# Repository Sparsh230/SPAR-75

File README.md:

# SPAR-75
A 75% keyboard 

Schmetic:

Keyboard matricks:

PCB:

3D model:

Cad Model Assembly(Plateless Mount):

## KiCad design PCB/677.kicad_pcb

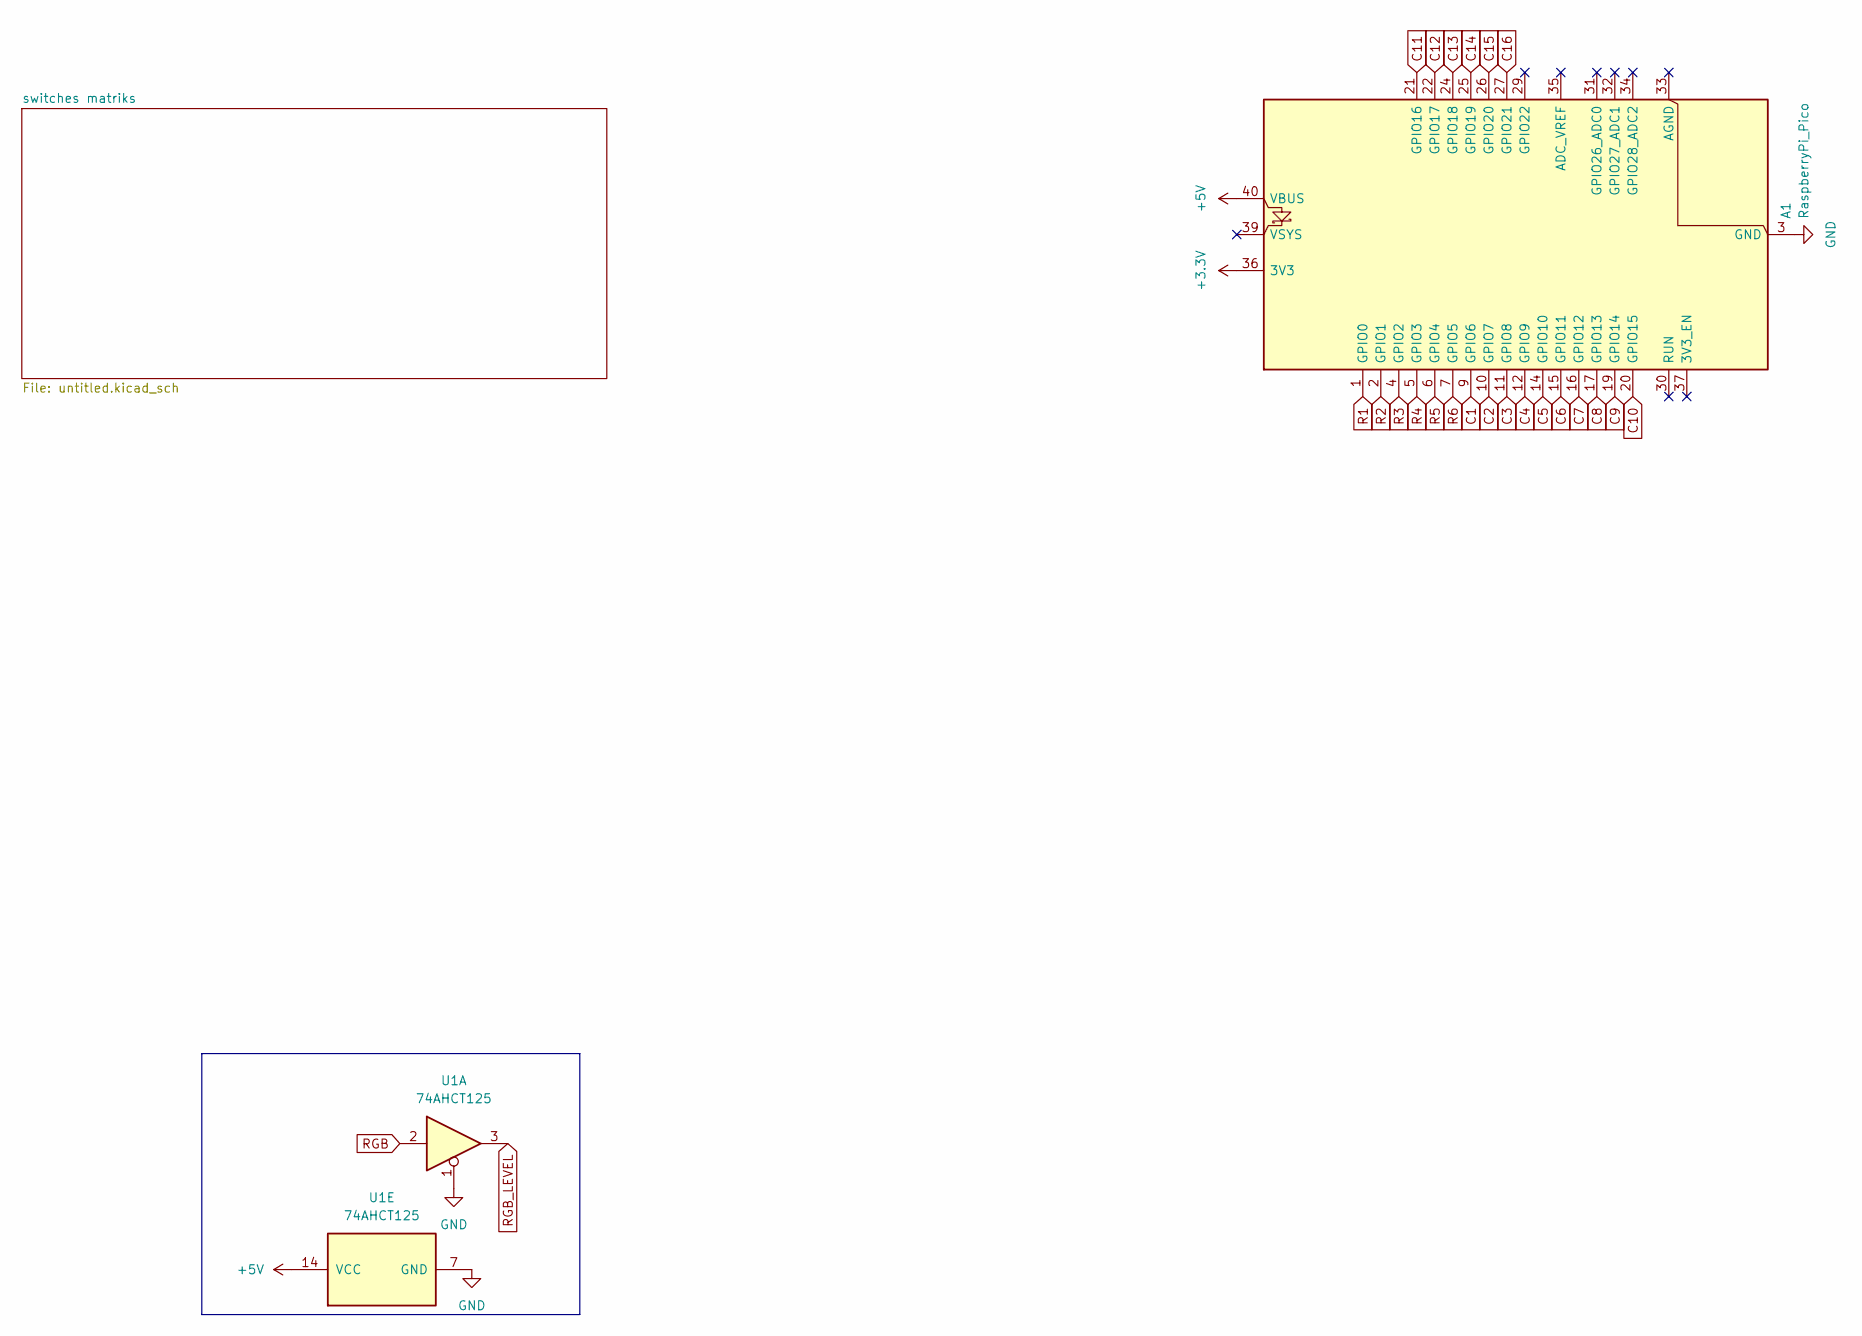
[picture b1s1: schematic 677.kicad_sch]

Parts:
A1: RaspberryPi_Pico; RaspberryPi_Pico_SMD
U1: 74AHCT125; ER_OLEDM0.91_1x-I2C

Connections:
+3.3V: A1.36 (3V3)
+5V: A1.40 (VBUS), U1.14 (VCC)
C1: A1.9 (GPIO6); also elsewhere on the board
C2: A1.10 (GPIO7); also elsewhere on the board
C3: A1.11 (GPIO8); also elsewhere on the board
C4: A1.12 (GPIO9); also elsewhere on the board
C5: A1.14 (GPIO10); also elsewhere on the board
C6: A1.15 (GPIO11); also elsewhere on the board
C7: A1.16 (GPIO12); also elsewhere on the board
C8: A1.17 (GPIO13); also elsewhere on the board
C9: A1.19 (GPIO14); also elsewhere on the board
C10: A1.20 (GPIO15); also elsewhere on the board
C11: A1.21 (GPIO16); also elsewhere on the board
C12: A1.22 (GPIO17); also elsewhere on the board
C13: A1.24 (GPIO18); also elsewhere on the board
C14: A1.25 (GPIO19); also elsewhere on the board
C15: A1.26 (GPIO20); also elsewhere on the board
C16: A1.27 (GPIO21); also elsewhere on the board
GND: A1.3 (GND), A1.8 (GND), A1.13 (GND), A1.18 (GND), A1.23 (GND), A1.28 (GND), A1.38 (GND), U1.1, U1.7 (GND)
R1: A1.1 (GPIO0); also elsewhere on the board
R2: A1.2 (GPIO1); also elsewhere on the board
R3: A1.4 (GPIO2); also elsewhere on the board
R4: A1.5 (GPIO3); also elsewhere on the board
R5: A1.6 (GPIO4); also elsewhere on the board
R6: A1.7 (GPIO5); also elsewhere on the board
RGB: U1.2
RGB_LEVEL: U1.3

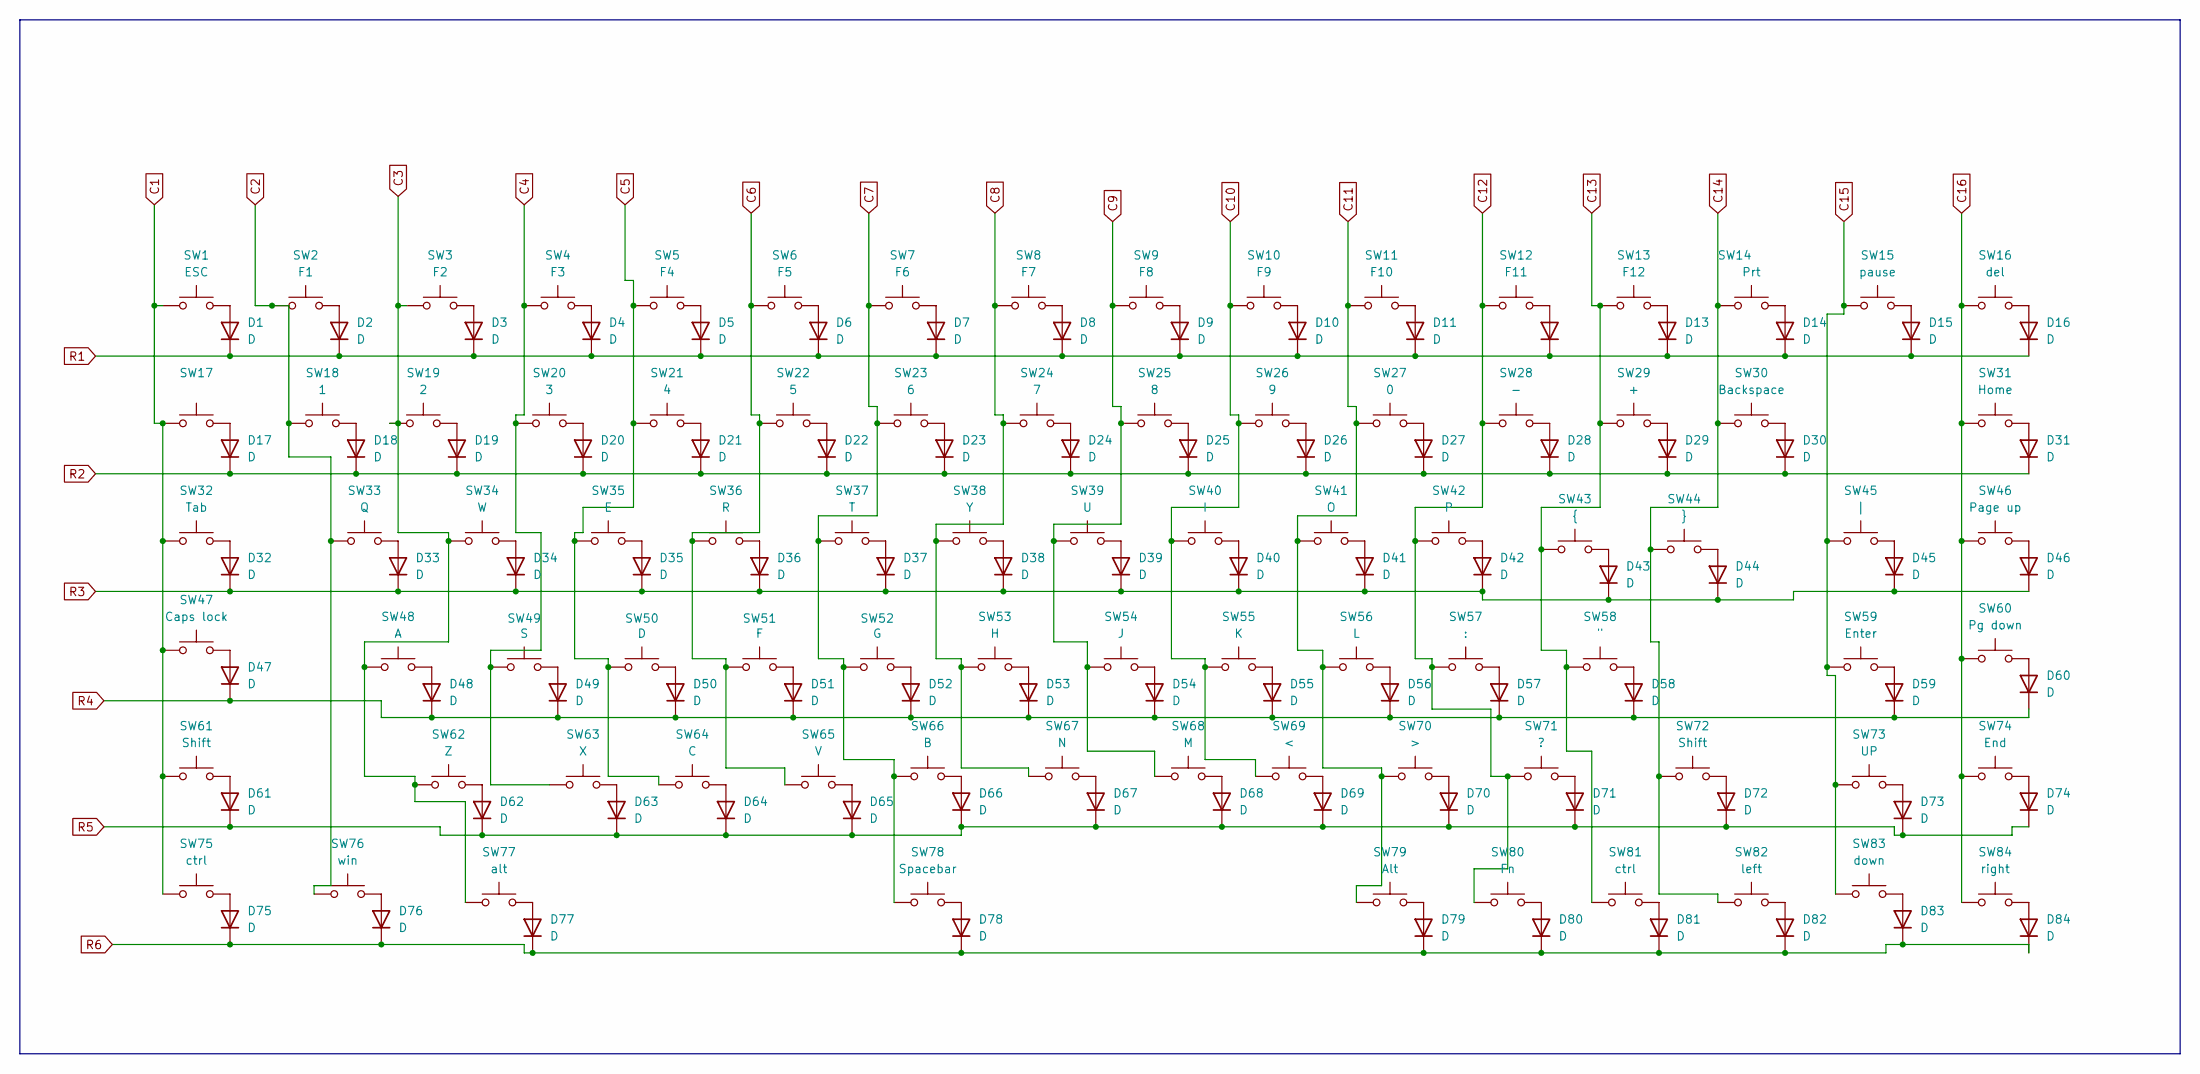
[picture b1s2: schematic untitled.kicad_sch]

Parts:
D1, D2, D3, D4, D5, D6, D7, D8, D9, D10, D11, D12, D13, D14, D15, D16, D17, D18, D19, D20, D21, D22, D23, D24, D25, D26, D27, D28, D29, D30, D31, D32, D33, D34, D35, D36, D37, D38, D39, D40, D41, D42, D43, D44, D45, D46, D47, D48, D49, D50, D51, D52, D53, D54, D55, D56, D57, D58, D59, D60, D61, D62, D63, D64, D65, D66, D67, D68, D69, D70, D71, D72, D73, D74, D75, D76, D77, D78, D79, D80, D81, D82, D83, D84: D; D_DO-35_SOD27_P7.62mm_Horizontal
SW1: ESC; SW_Cherry_MX_1.00u_PCB
SW2: F1; SW_Cherry_MX_1.00u_PCB
SW3: F2; SW_Cherry_MX_1.00u_PCB
SW4: F3; SW_Cherry_MX_1.00u_PCB
SW5: F4; SW_Cherry_MX_1.00u_PCB
SW6: F5; SW_Cherry_MX_1.00u_PCB
SW7: F6; SW_Cherry_MX_1.00u_PCB
SW8: F7; SW_Cherry_MX_1.00u_PCB
SW9: F8; SW_Cherry_MX_1.00u_PCB
SW10: F9; SW_Cherry_MX_1.00u_PCB
SW11: F10; SW_Cherry_MX_1.00u_PCB
SW12: F11; SW_Cherry_MX_1.00u_PCB
SW13: F12; SW_Cherry_MX_1.00u_PCB
SW14: Prt; SW_Cherry_MX_1.00u_PCB
SW15: pause; SW_Cherry_MX_1.00u_PCB
SW16: del; SW_Cherry_MX_1.00u_PCB
SW17: SW_Cherry_MX_1.00u_PCB
SW18: 1; SW_Cherry_MX_1.00u_PCB
SW19: 2; SW_Cherry_MX_1.00u_PCB
SW20: 3; SW_Cherry_MX_1.00u_PCB
SW21: 4; SW_Cherry_MX_1.00u_PCB
SW22: 5; SW_Cherry_MX_1.00u_PCB
SW23: 6; SW_Cherry_MX_1.00u_PCB
SW24: 7; SW_Cherry_MX_1.00u_PCB
SW25: 8; SW_Cherry_MX_1.00u_PCB
SW26: 9; SW_Cherry_MX_1.00u_PCB
SW27: 0; SW_Cherry_MX_1.00u_PCB
SW28: -; SW_Cherry_MX_1.00u_PCB
SW29: +; SW_Cherry_MX_1.00u_PCB
SW30: Backspace; SW_Cherry_MX_2.00u_PCB
SW31: Home; SW_Cherry_MX_1.00u_PCB
SW32: Tab; SW_Cherry_MX_1.50u_PCB
SW33: Q; SW_Cherry_MX_1.00u_PCB
SW34: W; SW_Cherry_MX_1.00u_PCB
SW35: E; SW_Cherry_MX_1.00u_PCB
SW36: R; SW_Cherry_MX_1.00u_PCB
SW37: T; SW_Cherry_MX_1.00u_PCB
SW38: Y; SW_Cherry_MX_1.00u_PCB
SW39: U; SW_Cherry_MX_1.00u_PCB
SW40: I; SW_Cherry_MX_1.00u_PCB
SW41: O; SW_Cherry_MX_1.00u_PCB
SW42: P; SW_Cherry_MX_1.00u_PCB
SW43: {; SW_Cherry_MX_1.00u_PCB
SW44: }; SW_Cherry_MX_1.00u_PCB
SW45: |; SW_Cherry_MX_1.50u_PCB
SW46: Page up; SW_Cherry_MX_1.00u_PCB
SW47: Caps lock; SW_Cherry_MX_1.75u_PCB
SW48: A; SW_Cherry_MX_1.00u_PCB
SW49: S; SW_Cherry_MX_1.00u_PCB
SW50: D; SW_Cherry_MX_1.00u_PCB
SW51: F; SW_Cherry_MX_1.00u_PCB
SW52: G; SW_Cherry_MX_1.00u_PCB
SW53: H; SW_Cherry_MX_1.00u_PCB
SW54: J; SW_Cherry_MX_1.00u_PCB
SW55: K; SW_Cherry_MX_1.00u_PCB
SW56: L; SW_Cherry_MX_1.00u_PCB
SW57: :; SW_Cherry_MX_1.00u_PCB
SW58: "; SW_Cherry_MX_1.00u_PCB
SW59: Enter; SW_Cherry_MX_2.25u_PCB
SW60: Pg down; SW_Cherry_MX_1.00u_PCB
SW61: Shift; SW_Cherry_MX_2.25u_PCB
SW62: Z; SW_Cherry_MX_1.00u_PCB
SW63: X; SW_Cherry_MX_1.00u_PCB
SW64: C; SW_Cherry_MX_1.00u_PCB
SW65: V; SW_Cherry_MX_1.00u_PCB
SW66: B; SW_Cherry_MX_1.00u_PCB
SW67: N; SW_Cherry_MX_1.00u_PCB
SW68: M; SW_Cherry_MX_1.00u_PCB
SW69: <; SW_Cherry_MX_1.00u_PCB
SW70: >; SW_Cherry_MX_1.00u_PCB
SW71: ?; SW_Cherry_MX_1.00u_PCB
SW72: Shift; SW_Cherry_MX_1.75u_PCB
SW73: UP; SW_Cherry_MX_1.00u_PCB
SW74: End; SW_Cherry_MX_1.00u_PCB
SW75: ctrl; SW_Cherry_MX_1.00u_PCB
SW76: win; SW_Cherry_MX_1.00u_PCB
SW77: alt; SW_Cherry_MX_1.00u_PCB
SW78: Spacebar; SW_Cherry_MX_6.25u_PCB
SW79: Alt; SW_Cherry_MX_1.25u_PCB
SW80: Fn; SW_Cherry_MX_1.25u_PCB
SW81: ctrl; SW_Cherry_MX_1.25u_PCB
SW82: left; SW_Cherry_MX_1.00u_PCB
SW83: down; SW_Cherry_MX_1.00u_PCB
SW84: right; SW_Cherry_MX_1.00u_PCB

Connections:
C1: SW1.1, SW17.1, SW32.1, SW47.1, SW61.1, SW75.1; also elsewhere on the board
C2: SW2.1, SW18.1, SW33.1, SW76.1; also elsewhere on the board
C3: SW3.1, SW19.1, SW34.1, SW48.1, SW62.1, SW77.1; also elsewhere on the board
C4: SW4.1, SW20.1, SW49.1, SW63.1; also elsewhere on the board
C5: SW5.1, SW21.1, SW35.1, SW50.1, SW64.1; also elsewhere on the board
C6: SW6.1, SW22.1, SW36.1, SW51.1, SW65.1; also elsewhere on the board
C7: SW7.1, SW23.1, SW37.1, SW52.1, SW66.1, SW78.1; also elsewhere on the board
C8: SW8.1, SW24.1, SW38.1, SW53.1, SW67.1; also elsewhere on the board
C9: SW9.1, SW25.1, SW39.1, SW54.1, SW68.1; also elsewhere on the board
C10: SW10.1, SW26.1, SW40.1, SW55.1, SW69.1; also elsewhere on the board
C11: SW11.1, SW27.1, SW41.1, SW56.1, SW70.1, SW79.1; also elsewhere on the board
C12: SW12.1, SW28.1, SW42.1, SW57.1, SW71.1, SW80.1; also elsewhere on the board
C13: SW13.1, SW29.1, SW43.1, SW58.1, SW81.1; also elsewhere on the board
C14: SW14.1, SW30.1, SW44.1, SW72.1, SW82.1; also elsewhere on the board
C15: SW15.1, SW45.1, SW59.1, SW73.1, SW83.1; also elsewhere on the board
C16: SW16.1, SW31.1, SW46.1, SW60.1, SW74.1, SW84.1; also elsewhere on the board
unnamed: D1.2 (A), SW1.2
unnamed: D2.2 (A), SW2.2
unnamed: D3.2 (A), SW3.2
unnamed: D4.2 (A), SW4.2
unnamed: D5.2 (A), SW5.2
unnamed: D6.2 (A), SW6.2
unnamed: D7.2 (A), SW7.2
unnamed: D8.2 (A), SW8.2
unnamed: D9.2 (A), SW9.2
unnamed: D10.2 (A), SW10.2
unnamed: D11.2 (A), SW11.2
unnamed: D12.2 (A), SW12.2
unnamed: D13.2 (A), SW13.2
unnamed: D14.2 (A), SW14.2
unnamed: D15.2 (A), SW15.2
unnamed: D16.2 (A), SW16.2
unnamed: D17.2 (A), SW17.2
unnamed: D18.2 (A), SW18.2
unnamed: D19.2 (A), SW19.2
unnamed: D20.2 (A), SW20.2
unnamed: D21.2 (A), SW21.2
unnamed: D22.2 (A), SW22.2
unnamed: D23.2 (A), SW23.2
unnamed: D24.2 (A), SW24.2
unnamed: D25.2 (A), SW25.2
unnamed: D26.2 (A), SW26.2
unnamed: D27.2 (A), SW27.2
unnamed: D28.2 (A), SW28.2
unnamed: D29.2 (A), SW29.2
unnamed: D30.2 (A), SW30.2
unnamed: D31.2 (A), SW31.2
unnamed: D32.2 (A), SW32.2
unnamed: D33.2 (A), SW33.2
unnamed: D34.2 (A), SW34.2
unnamed: D35.2 (A), SW35.2
unnamed: D36.2 (A), SW36.2
unnamed: D37.2 (A), SW37.2
unnamed: D38.2 (A), SW38.2
unnamed: D39.2 (A), SW39.2
unnamed: D40.2 (A), SW40.2
unnamed: D41.2 (A), SW41.2
unnamed: D42.2 (A), SW42.2
unnamed: D43.2 (A), SW43.2
unnamed: D44.2 (A), SW44.2
unnamed: D45.2 (A), SW45.2
unnamed: D46.2 (A), SW46.2
unnamed: D47.2 (A), SW47.2
unnamed: D48.2 (A), SW48.2
unnamed: D49.2 (A), SW49.2
unnamed: D50.2 (A), SW50.2
unnamed: D51.2 (A), SW51.2
unnamed: D52.2 (A), SW52.2
unnamed: D53.2 (A), SW53.2
unnamed: D54.2 (A), SW54.2
unnamed: D55.2 (A), SW55.2
unnamed: D56.2 (A), SW56.2
unnamed: D57.2 (A), SW57.2
unnamed: D58.2 (A), SW58.2
unnamed: D59.2 (A), SW59.2
unnamed: D60.2 (A), SW60.2
unnamed: D61.2 (A), SW61.2
unnamed: D62.2 (A), SW62.2
unnamed: D63.2 (A), SW63.2
unnamed: D64.2 (A), SW64.2
unnamed: D65.2 (A), SW65.2
unnamed: D66.2 (A), SW66.2
unnamed: D67.2 (A), SW67.2
unnamed: D68.2 (A), SW68.2
unnamed: D69.2 (A), SW69.2
unnamed: D70.2 (A), SW70.2
unnamed: D71.2 (A), SW71.2
unnamed: D72.2 (A), SW72.2
unnamed: D73.2 (A), SW73.2
unnamed: D74.2 (A), SW74.2
unnamed: D75.2 (A), SW75.2
unnamed: D76.2 (A), SW76.2
unnamed: D77.2 (A), SW77.2
unnamed: D78.2 (A), SW78.2
unnamed: D79.2 (A), SW79.2
unnamed: D80.2 (A), SW80.2
unnamed: D81.2 (A), SW81.2
unnamed: D82.2 (A), SW82.2
unnamed: D83.2 (A), SW83.2
unnamed: D84.2 (A), SW84.2
R1: D1.1 (K), D2.1 (K), D3.1 (K), D4.1 (K), D5.1 (K), D6.1 (K), D7.1 (K), D8.1 (K), D9.1 (K), D10.1 (K), D11.1 (K), D12.1 (K), D13.1 (K), D14.1 (K), D15.1 (K), D16.1 (K); also elsewhere on the board
R2: D17.1 (K), D18.1 (K), D19.1 (K), D20.1 (K), D21.1 (K), D22.1 (K), D23.1 (K), D24.1 (K), D25.1 (K), D26.1 (K), D27.1 (K), D28.1 (K), D29.1 (K), D30.1 (K), D31.1 (K); also elsewhere on the board
R3: D32.1 (K), D33.1 (K), D34.1 (K), D35.1 (K), D36.1 (K), D37.1 (K), D38.1 (K), D39.1 (K), D40.1 (K), D41.1 (K), D42.1 (K), D43.1 (K), D44.1 (K), D45.1 (K), D46.1 (K); also elsewhere on the board
R4: D47.1 (K), D48.1 (K), D49.1 (K), D50.1 (K), D51.1 (K), D52.1 (K), D53.1 (K), D54.1 (K), D55.1 (K), D56.1 (K), D57.1 (K), D58.1 (K), D59.1 (K), D60.1 (K); also elsewhere on the board
R5: D61.1 (K), D62.1 (K), D63.1 (K), D64.1 (K), D65.1 (K), D66.1 (K), D67.1 (K), D68.1 (K), D69.1 (K), D70.1 (K), D71.1 (K), D72.1 (K), D73.1 (K), D74.1 (K); also elsewhere on the board
R6: D75.1 (K), D76.1 (K), D77.1 (K), D78.1 (K), D79.1 (K), D80.1 (K), D81.1 (K), D82.1 (K), D83.1 (K), D84.1 (K); also elsewhere on the board

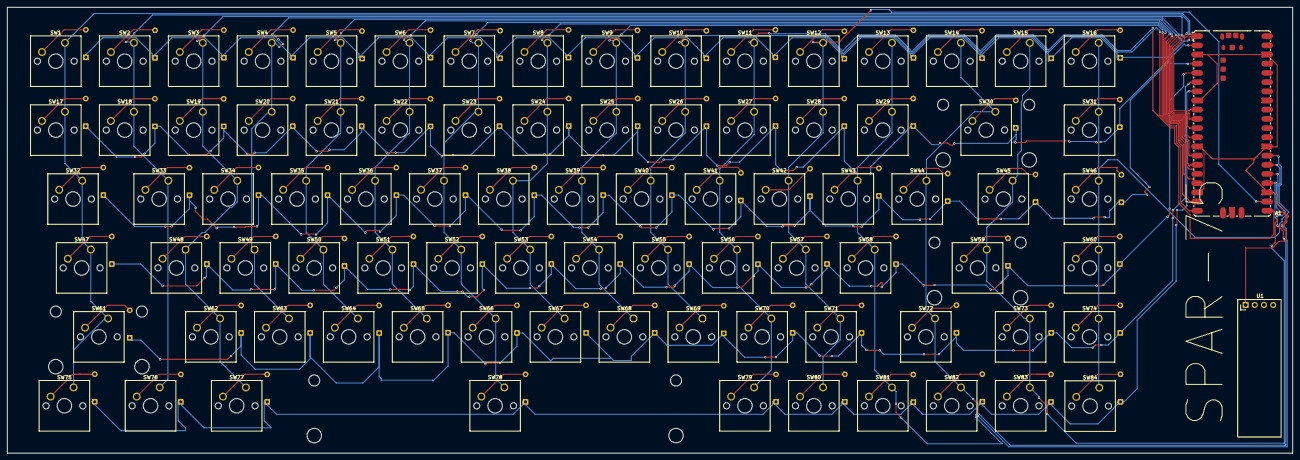
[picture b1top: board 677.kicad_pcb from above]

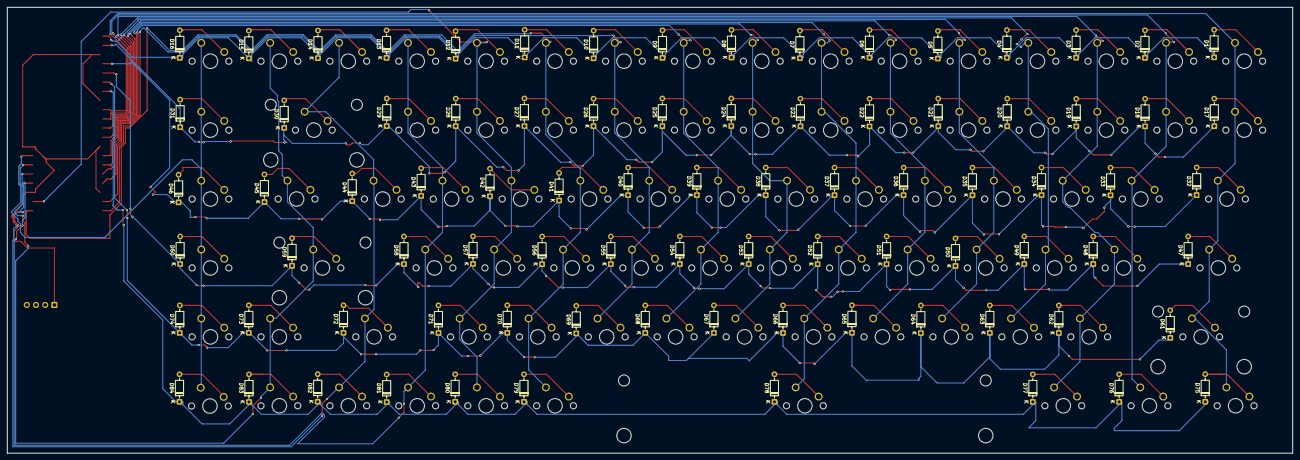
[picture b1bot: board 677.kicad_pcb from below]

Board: 2 copper layers, 355.3 x 123.2 mm, 170 parts (84 on the bottom side), 107 nets.

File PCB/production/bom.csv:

Designator,Footprint,Quantity,Value,LCSC Part #
A1,RaspberryPi_Pico_SMD,1,RaspberryPi_Pico,
"D1, D10, D11, D12, D13, D14, D15, D16, D17, D18, D19, D2, D20, D21, D22, D23, D24, D25, D26, D27, D28, D29, D3, D30, D31, D32, D33, D34, D35, D36, D37, D38, D39, D4, D40, D41, D42, D43, D44, D45, D46, D47, D48, D49, D5, D50, D51, D52, D53, D54, D55, D56, D57, D58, D59, D6, D60, D61, D62, D63, D64, D65, D66, D67, D68, D69, D7, D70, D71, D72, D73, D74, D75, D76, D77, D78, D79, D8, D80, D81, D82, D83, D84, D9",D_DO-35_SOD27_P7.62mm_Horizontal,84,D,
SW1,SW_Cherry_MX_1.00u_PCB,1,ESC,
SW10,SW_Cherry_MX_1.00u_PCB,1,F9,
SW11,SW_Cherry_MX_1.00u_PCB,1,F10,
SW12,SW_Cherry_MX_1.00u_PCB,1,F11,
SW13,SW_Cherry_MX_1.00u_PCB,1,F12,
SW14,SW_Cherry_MX_1.00u_PCB,1,Prt,
SW15,SW_Cherry_MX_1.00u_PCB,1,pause,
SW16,SW_Cherry_MX_1.00u_PCB,1,del,
SW17,SW_Cherry_MX_1.00u_PCB,1,~,
SW18,SW_Cherry_MX_1.00u_PCB,1,1,
SW19,SW_Cherry_MX_1.00u_PCB,1,2,
SW2,SW_Cherry_MX_1.00u_PCB,1,F1,
SW20,SW_Cherry_MX_1.00u_PCB,1,3,
SW21,SW_Cherry_MX_1.00u_PCB,1,4,
SW22,SW_Cherry_MX_1.00u_PCB,1,5,
SW23,SW_Cherry_MX_1.00u_PCB,1,6,
SW24,SW_Cherry_MX_1.00u_PCB,1,7,
SW25,SW_Cherry_MX_1.00u_PCB,1,8,
SW26,SW_Cherry_MX_1.00u_PCB,1,9,
SW27,SW_Cherry_MX_1.00u_PCB,1,0,
SW28,SW_Cherry_MX_1.00u_PCB,1,-,
SW29,SW_Cherry_MX_1.00u_PCB,1,+,
SW3,SW_Cherry_MX_1.00u_PCB,1,F2,
SW30,SW_Cherry_MX_2.00u_PCB,1,Backspace,
SW31,SW_Cherry_MX_1.00u_PCB,1,Home,
SW32,SW_Cherry_MX_1.50u_PCB,1,Tab,
SW33,SW_Cherry_MX_1.00u_PCB,1,Q,
SW34,SW_Cherry_MX_1.00u_PCB,1,W,
SW35,SW_Cherry_MX_1.00u_PCB,1,E,
SW36,SW_Cherry_MX_1.00u_PCB,1,R,
SW37,SW_Cherry_MX_1.00u_PCB,1,T,
SW38,SW_Cherry_MX_1.00u_PCB,1,Y,
SW39,SW_Cherry_MX_1.00u_PCB,1,U,
SW4,SW_Cherry_MX_1.00u_PCB,1,F3,
SW40,SW_Cherry_MX_1.00u_PCB,1,I,
SW41,SW_Cherry_MX_1.00u_PCB,1,O,
SW42,SW_Cherry_MX_1.00u_PCB,1,P,
SW43,SW_Cherry_MX_1.00u_PCB,1,{,
SW44,SW_Cherry_MX_1.00u_PCB,1,},
SW45,SW_Cherry_MX_1.50u_PCB,1,|,
SW46,SW_Cherry_MX_1.00u_PCB,1,Page up,
SW47,SW_Cherry_MX_1.75u_PCB,1,Caps lock,
SW48,SW_Cherry_MX_1.00u_PCB,1,A,
SW49,SW_Cherry_MX_1.00u_PCB,1,S,
SW5,SW_Cherry_MX_1.00u_PCB,1,F4,
SW50,SW_Cherry_MX_1.00u_PCB,1,D,
SW51,SW_Cherry_MX_1.00u_PCB,1,F,
SW52,SW_Cherry_MX_1.00u_PCB,1,G,
SW53,SW_Cherry_MX_1.00u_PCB,1,H,
SW54,SW_Cherry_MX_1.00u_PCB,1,J,
SW55,SW_Cherry_MX_1.00u_PCB,1,K,
SW56,SW_Cherry_MX_1.00u_PCB,1,L,
SW57,SW_Cherry_MX_1.00u_PCB,1,:,
SW58,SW_Cherry_MX_1.00u_PCB,1,"""",
SW59,SW_Cherry_MX_2.25u_PCB,1,Enter,
SW6,SW_Cherry_MX_1.00u_PCB,1,F5,
SW60,SW_Cherry_MX_1.00u_PCB,1,Pg down,
SW61,SW_Cherry_MX_2.25u_PCB,1,Shift,
SW62,SW_Cherry_MX_1.00u_PCB,1,Z,
SW63,SW_Cherry_MX_1.00u_PCB,1,X,
SW64,SW_Cherry_MX_1.00u_PCB,1,C,
SW65,SW_Cherry_MX_1.00u_PCB,1,V,
SW66,SW_Cherry_MX_1.00u_PCB,1,B,
SW67,SW_Cherry_MX_1.00u_PCB,1,N,
SW68,SW_Cherry_MX_1.00u_PCB,1,M,
SW69,SW_Cherry_MX_1.00u_PCB,1,<,
SW7,SW_Cherry_MX_1.00u_PCB,1,F6,
SW70,SW_Cherry_MX_1.00u_PCB,1,>,
SW71,SW_Cherry_MX_1.00u_PCB,1,?,
SW72,SW_Cherry_MX_1.75u_PCB,1,Shift,
SW73,SW_Cherry_MX_1.00u_PCB,1,UP,
SW74,SW_Cherry_MX_1.00u_PCB,1,End,
SW75,SW_Cherry_MX_1.00u_PCB,1,ctrl,
SW76,SW_Cherry_MX_1.00u_PCB,1,win,
SW77,SW_Cherry_MX_1.00u_PCB,1,alt,
SW78,SW_Cherry_MX_6.25u_PCB,1,Spacebar,
SW79,SW_Cherry_MX_1.25u_PCB,1,Alt,
SW8,SW_Cherry_MX_1.00u_PCB,1,F7,
SW80,SW_Cherry_MX_1.25u_PCB,1,Fn,
SW81,SW_Cherry_MX_1.25u_PCB,1,ctrl,
SW82,SW_Cherry_MX_1.00u_PCB,1,left,
SW83,SW_Cherry_MX_1.00u_PCB,1,down,
SW84,SW_Cherry_MX_1.00u_PCB,1,right,
SW9,SW_Cherry_MX_1.00u_PCB,1,F8,
U1,ER_OLEDM0.91_1x-I2C,1,74AHCT125,
